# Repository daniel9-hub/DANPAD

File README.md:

# DANPAD
Hello, this is my submission for hackpad. I hope you'll like it :)
# Picture of the finished Hackpad

# Features
- 6 keys
- EC11 rotary encoder for volume adjusting
- 2 SK6812 MINI RGB LEDs
- a 3d printed case
# CAD Model
I made the model for the case in Onshape. It has 4 pieces: a bottom and mid plate(separated in case i needed to change
something so that i dont have to reprint the entire case), a top plate and a knob

Here is the case without electronics

# PCB
I made the pcb in KiCad. I used the image converter in KiCad for the pictures.
|Schematic|PCB|
|---------|---|
|||
# Firmware
I wrote the code with KMK. The rotary encoder changes the volume and the keys do functions that i'm going to change according my needs.
# BOM
- 1x Seeed XIAO RP2040
- 6x MX-Style switches
- 6x Blank DSA keycaps
- 2x SK6812 MINI-E LEDs
- 1x EC11 Rotary encoder
- 4x M3x16mm screws
- 4x/8x M3x5mx4mm heatset inserts (i'm not sure how many i'll need)
- 1x 3d printed case
- 1x PCB
# Extra stuff
I might change the screw hole size on the case since i'm not sure how will the screws and heatset inserts fit. I also forgot to add a ground trace to the switches so I had to solder a wire to one of the switches right pin and connect it to the xiaos ground pin.

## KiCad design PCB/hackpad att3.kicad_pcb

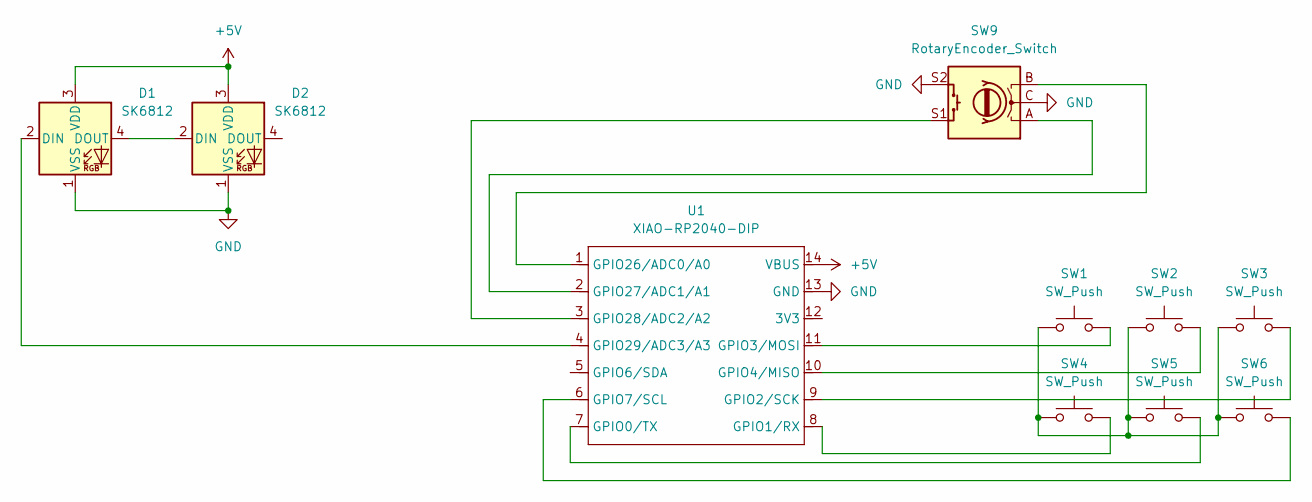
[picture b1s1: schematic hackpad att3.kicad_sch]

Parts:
D1, D2: SK6812; LED_SK6812MINI_PLCC4_3.5x3.5mm_P1.75mm
SW1, SW2, SW3, SW4, SW5, SW6: SW_Push; SW_Cherry_MX_1.00u_PCB
SW9: RotaryEncoder_Switch; RotaryEncoder_Alps_EC11E-Switch_Vertical_H20mm
U1: XIAO-RP2040-DIP

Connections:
+5V: D1.3 (VDD), D2.3 (VDD), U1.14 (VBUS)
GND: D1.1 (VSS), D2.1 (VSS), SW9.C, SW9.S2, U1.13 (GND)
unnamed: D1.2 (DIN), U1.4 (GPIO29/ADC3/A3)
unnamed: D1.4 (DOUT), D2.2 (DIN)
unnamed: SW1.1, SW2.1, SW3.1, SW4.1, SW5.1, SW6.1
unnamed: SW5.2, U1.7 (GPIO0/TX)
unnamed: SW4.2, U1.8 (GPIO1/RX)
unnamed: SW3.2, U1.9 (GPIO2/SCK)
unnamed: SW1.2, U1.11 (GPIO3/MOSI)
unnamed: SW2.2, U1.10 (GPIO4/MISO)
unnamed: SW6.2, U1.6 (GPIO7/SCL)
unnamed: SW9.B, U1.1 (GPIO26/ADC0/A0)
unnamed: SW9.A, U1.2 (GPIO27/ADC1/A1)
unnamed: SW9.S1, U1.3 (GPIO28/ADC2/A2)

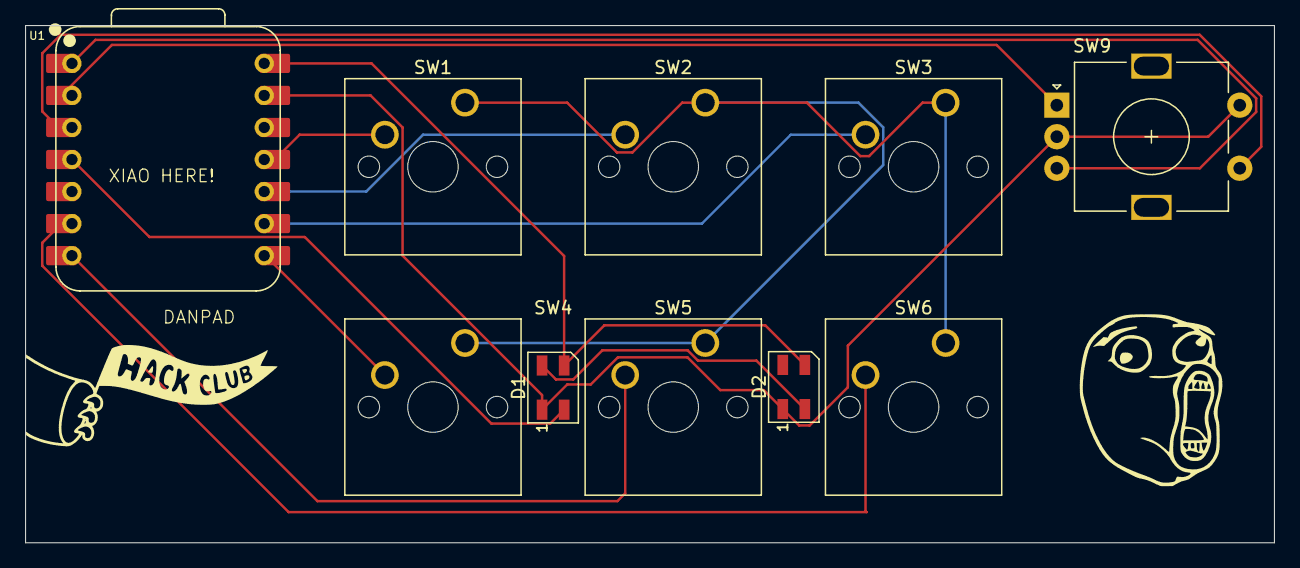
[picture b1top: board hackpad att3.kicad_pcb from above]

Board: 2 copper layers, 99.0 x 41.0 mm, 10 parts (0 on the bottom side), 14 nets.

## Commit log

2026-02-02 Add CODE folder
2026-02-02 Add CAD folder
2026-02-02 Add PCB folder
2026-04-15 Updated some stuff
